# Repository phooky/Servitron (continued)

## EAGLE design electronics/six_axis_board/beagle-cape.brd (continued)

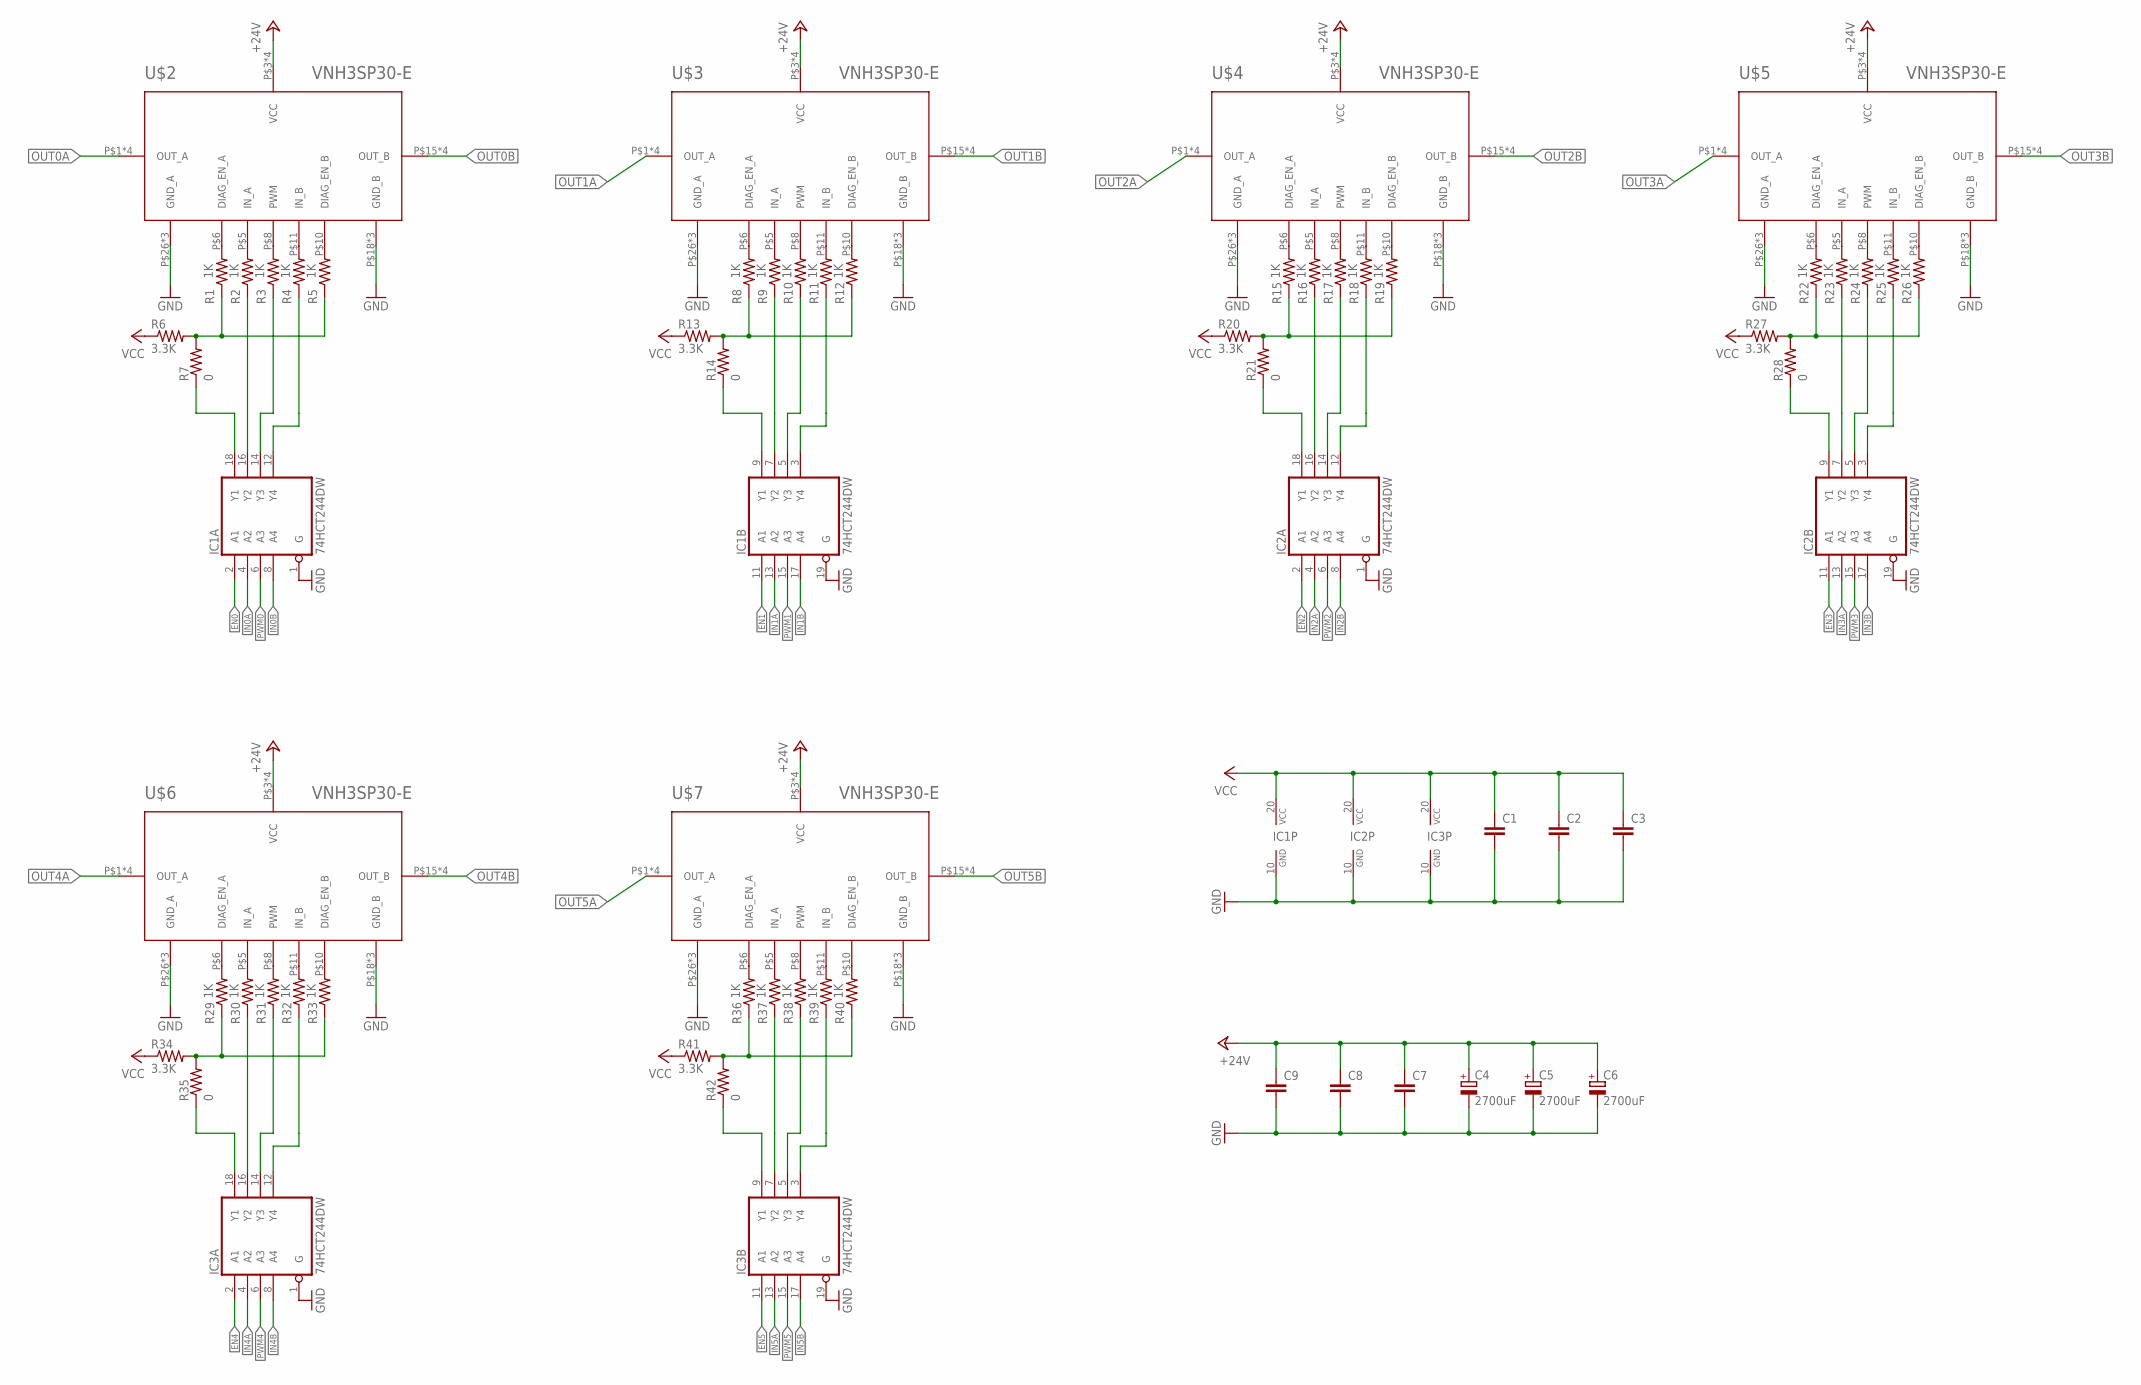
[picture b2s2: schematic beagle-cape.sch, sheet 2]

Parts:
C1, C2, C3, C7, C8, C9: C-EUC1206; C1206
C4, C5, C6: 2700uF; E5-13
IC1, IC2, IC3: 74HCT244DW; SO20W
R1, R2, R3, R4, R5, R8, R9, R10, R11, R12, R15, R16, R17, R18, R19, R22, R23, R24, R25, R26, R29, R30, R31, R32, R33, R36, R37, R38, R39, R40: 1K; R1206
R6, R13, R20, R27, R34, R41: 3.3K; R1206
R7, R14, R21, R28, R35, R42: 0; R1206
U$2, U$3, U$4, U$5, U$6, U$7: VNH3SP30-E; MULTIPOWER-SO-30

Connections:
+24V: C4.+, C5.+, C6.+, C7.1, C8.1, C9.1, U$2.P$3 (VCC), U$2.P$13 (VCC), U$2.P$23 (VCC), U$2.T$3 (VCC), U$3.P$3 (VCC), U$3.P$13 (VCC), U$3.P$23 (VCC), U$3.T$3 (VCC), U$4.P$3 (VCC), U$4.P$13 (VCC), U$4.P$23 (VCC), U$4.T$3 (VCC), U$5.P$3 (VCC), U$5.P$13 (VCC), U$5.P$23 (VCC), U$5.T$3 (VCC), U$6.P$3 (VCC), U$6.P$13 (VCC), U$6.P$23 (VCC), U$6.T$3 (VCC), U$7.P$3 (VCC), U$7.P$13 (VCC), U$7.P$23 (VCC), U$7.T$3 (VCC); also elsewhere on the board
EN0: IC1.2 (A1); also elsewhere on the board
EN1: IC1.11 (A1); also elsewhere on the board
EN2: IC2.2 (A1); also elsewhere on the board
EN3: IC2.11 (A1); also elsewhere on the board
EN4: IC3.2 (A1); also elsewhere on the board
EN5: IC3.11 (A1); also elsewhere on the board
GND: C1.2, C2.2, C3.2, C4.-, C5.-, C6.-, C7.2, C8.2, C9.2, IC1.1 (G), IC1.10 (GND), IC1.19 (G), IC2.1 (G), IC2.10 (GND), IC2.19 (G), IC3.1 (G), IC3.10 (GND), IC3.19 (G), U$2.P$18 (GND_B), U$2.P$19 (GND_B), U$2.P$20 (GND_B), U$2.P$26 (GND_A), U$2.P$27 (GND_A), U$2.P$28 (GND_A), U$3.P$18 (GND_B), U$3.P$19 (GND_B), U$3.P$20 (GND_B), U$3.P$26 (GND_A), U$3.P$27 (GND_A), U$3.P$28 (GND_A), U$4.P$18 (GND_B), U$4.P$19 (GND_B), U$4.P$20 (GND_B), U$4.P$26 (GND_A), U$4.P$27 (GND_A), U$4.P$28 (GND_A), U$5.P$18 (GND_B), U$5.P$19 (GND_B), U$5.P$20 (GND_B), U$5.P$26 (GND_A), U$5.P$27 (GND_A), U$5.P$28 (GND_A), U$6.P$18 (GND_B), U$6.P$19 (GND_B), U$6.P$20 (GND_B), U$6.P$26 (GND_A), U$6.P$27 (GND_A), U$6.P$28 (GND_A), U$7.P$18 (GND_B), U$7.P$19 (GND_B), U$7.P$20 (GND_B), U$7.P$26 (GND_A), U$7.P$27 (GND_A), U$7.P$28 (GND_A); also elsewhere on the board
IN0A: IC1.4 (A2); also elsewhere on the board
IN0B: IC1.8 (A4); also elsewhere on the board
IN1A: IC1.13 (A2); also elsewhere on the board
IN1B: IC1.17 (A4); also elsewhere on the board
IN2A: IC2.4 (A2); also elsewhere on the board
IN2B: IC2.8 (A4); also elsewhere on the board
IN3A: IC2.13 (A2); also elsewhere on the board
IN3B: IC2.17 (A4); also elsewhere on the board
IN4A: IC3.4 (A2); also elsewhere on the board
IN4B: IC3.8 (A4); also elsewhere on the board
IN5A: IC3.13 (A2); also elsewhere on the board
IN5B: IC3.17 (A4); also elsewhere on the board
unnamed: R1.2, U$2.P$6 (DIAG_EN_A)
unnamed: R1.1, R5.1, R6.2, R7.2
unnamed: IC1.18 (Y1), R7.1
unnamed: IC1.16 (Y2), R2.1
unnamed: IC1.14 (Y3), R3.1
unnamed: IC1.12 (Y4), R4.1
unnamed: R2.2, U$2.P$5 (IN_A)
unnamed: R3.2, U$2.P$8 (PWM)
unnamed: R4.2, U$2.P$11 (IN_B)
unnamed: R5.2, U$2.P$10 (DIAG_EN_B)
unnamed: R8.2, U$3.P$6 (DIAG_EN_A)
unnamed: R8.1, R12.1, R13.2, R14.2
unnamed: IC1.9 (Y1), R14.1
unnamed: IC1.7 (Y2), R9.1
unnamed: IC1.5 (Y3), R10.1
unnamed: IC1.3 (Y4), R11.1
unnamed: R39.2, U$7.P$11 (IN_B)
unnamed: R38.2, U$7.P$8 (PWM)
unnamed: R37.2, U$7.P$5 (IN_A)
unnamed: R40.2, U$7.P$10 (DIAG_EN_B)
unnamed: R15.2, U$4.P$6 (DIAG_EN_A)
unnamed: R15.1, R19.1, R20.2, R21.2
unnamed: IC2.18 (Y1), R21.1
unnamed: IC2.16 (Y2), R16.1
unnamed: IC2.14 (Y3), R17.1
unnamed: IC2.12 (Y4), R18.1
unnamed: R12.2, U$3.P$10 (DIAG_EN_B)
unnamed: R11.2, U$3.P$11 (IN_B)
unnamed: R16.2, U$4.P$5 (IN_A)
unnamed: R17.2, U$4.P$8 (PWM)
unnamed: R18.2, U$4.P$11 (IN_B)
unnamed: R19.2, U$4.P$10 (DIAG_EN_B)
unnamed: R22.2, U$5.P$6 (DIAG_EN_A)
unnamed: R22.1, R26.1, R27.2, R28.2
unnamed: IC2.9 (Y1), R28.1
unnamed: IC2.7 (Y2), R23.1
unnamed: IC2.5 (Y3), R24.1
unnamed: IC2.3 (Y4), R25.1
unnamed: R10.2, U$3.P$8 (PWM)
unnamed: R9.2, U$3.P$5 (IN_A)
unnamed: R29.2, U$6.P$6 (DIAG_EN_A)
unnamed: R29.1, R33.1, R34.2, R35.2
unnamed: IC3.18 (Y1), R35.1
unnamed: IC3.16 (Y2), R30.1
unnamed: IC3.14 (Y3), R31.1
unnamed: IC3.12 (Y4), R32.1
unnamed: R26.2, U$5.P$10 (DIAG_EN_B)
unnamed: R25.2, U$5.P$11 (IN_B)
unnamed: R30.2, U$6.P$5 (IN_A)
unnamed: R31.2, U$6.P$8 (PWM)
unnamed: R32.2, U$6.P$11 (IN_B)
unnamed: R33.2, U$6.P$10 (DIAG_EN_B)
unnamed: R36.2, U$7.P$6 (DIAG_EN_A)
unnamed: R36.1, R40.1, R41.2, R42.2
unnamed: IC3.9 (Y1), R42.1
unnamed: IC3.7 (Y2), R37.1
unnamed: IC3.5 (Y3), R38.1
unnamed: IC3.3 (Y4), R39.1
unnamed: R24.2, U$5.P$8 (PWM)
unnamed: R23.2, U$5.P$5 (IN_A)
OUT0A: U$2.P$1 (OUT_A), U$2.P$25 (OUT_A), U$2.P$30 (OUT_A), U$2.T$1 (OUT_A); also elsewhere on the board
OUT0B: U$2.P$15 (OUT_B), U$2.P$16 (OUT_B), U$2.P$21 (OUT_B), U$2.T$2 (OUT_B); also elsewhere on the board
OUT1A: U$3.P$1 (OUT_A), U$3.P$25 (OUT_A), U$3.P$30 (OUT_A), U$3.T$1 (OUT_A); also elsewhere on the board
OUT1B: U$3.P$15 (OUT_B), U$3.P$16 (OUT_B), U$3.P$21 (OUT_B), U$3.T$2 (OUT_B); also elsewhere on the board
OUT2A: U$4.P$1 (OUT_A), U$4.P$25 (OUT_A), U$4.P$30 (OUT_A), U$4.T$1 (OUT_A); also elsewhere on the board
OUT2B: U$4.P$15 (OUT_B), U$4.P$16 (OUT_B), U$4.P$21 (OUT_B), U$4.T$2 (OUT_B); also elsewhere on the board
OUT3A: U$5.P$1 (OUT_A), U$5.P$25 (OUT_A), U$5.P$30 (OUT_A), U$5.T$1 (OUT_A); also elsewhere on the board
OUT3B: U$5.P$15 (OUT_B), U$5.P$16 (OUT_B), U$5.P$21 (OUT_B), U$5.T$2 (OUT_B); also elsewhere on the board
OUT4A: U$6.P$1 (OUT_A), U$6.P$25 (OUT_A), U$6.P$30 (OUT_A), U$6.T$1 (OUT_A); also elsewhere on the board
OUT4B: U$6.P$15 (OUT_B), U$6.P$16 (OUT_B), U$6.P$21 (OUT_B), U$6.T$2 (OUT_B); also elsewhere on the board
OUT5A: U$7.P$1 (OUT_A), U$7.P$25 (OUT_A), U$7.P$30 (OUT_A), U$7.T$1 (OUT_A); also elsewhere on the board
OUT5B: U$7.P$15 (OUT_B), U$7.P$16 (OUT_B), U$7.P$21 (OUT_B), U$7.T$2 (OUT_B); also elsewhere on the board
PWM0: IC1.6 (A3); also elsewhere on the board
PWM1: IC1.15 (A3); also elsewhere on the board
PWM2: IC2.6 (A3); also elsewhere on the board
PWM3: IC2.15 (A3); also elsewhere on the board
PWM4: IC3.6 (A3); also elsewhere on the board
PWM5: IC3.15 (A3); also elsewhere on the board
VCC: C1.1, C2.1, C3.1, IC1.20 (VCC), IC2.20 (VCC), IC3.20 (VCC), R6.1, R13.1, R20.1, R27.1, R34.1, R41.1; also elsewhere on the board

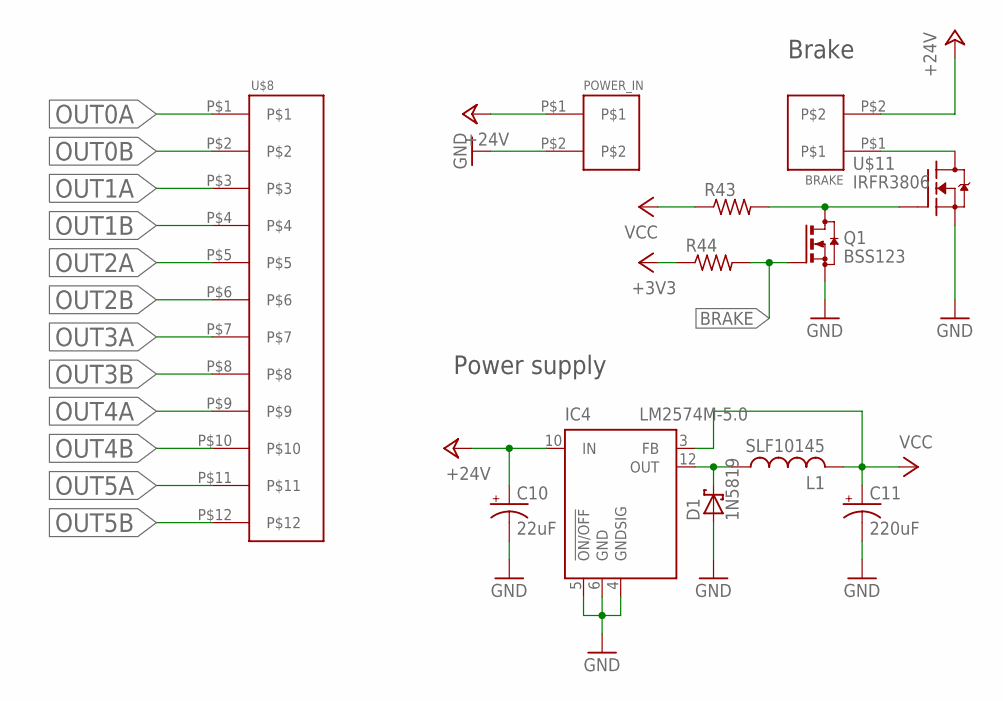
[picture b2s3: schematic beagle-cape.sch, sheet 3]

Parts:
BRAKE: PINHEAD-5MM-1X2; 5MM-HEADER-2
C10: 22uF; SANYO-OSCON_SMD_E7
C11: 220uF; SANYO-OSCON_SMD_F8
D1: 1N5819; SOD-123
IC4: LM2574M-5.0; SO14W
L1: SLF10145; SMD10145
POWER_IN: PINHEAD-5MM-1X2; 5MM-HEADER-2
Q1: BSS123; SOT23
R43, R44: R-US_R1206; R1206
U$8: PINHEAD-0.2IN-1X12; 0.2IN-TERMINAL-BLOCK-12
U$11: IRFR3806; TO252

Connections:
+3V3: R44.1; also elsewhere on the board
+24V: BRAKE.P$2, C10.+, IC4.10 (IN), POWER_IN.P$1; also elsewhere on the board
BRAKE: Q1.1 (G), R44.2; also elsewhere on the board
GND: C10.-, C11.-, D1.A, IC4.4 (GNDSIG), IC4.5 (!ON/OFF), IC4.6 (GND), POWER_IN.P$2, Q1.2 (S), U$11.2 (S); also elsewhere on the board
unnamed: D1.C, IC4.12 (OUT), L1.P$1 (1)
unnamed: BRAKE.P$1, U$11.3 (D)
unnamed: Q1.3 (D), R43.2, U$11.1 (G)
OUT0A: U$8.P$1; also elsewhere on the board
OUT0B: U$8.P$2; also elsewhere on the board
OUT1A: U$8.P$3; also elsewhere on the board
OUT1B: U$8.P$4; also elsewhere on the board
OUT2A: U$8.P$5; also elsewhere on the board
OUT2B: U$8.P$6; also elsewhere on the board
OUT3A: U$8.P$7; also elsewhere on the board
OUT3B: U$8.P$8; also elsewhere on the board
OUT4A: U$8.P$9; also elsewhere on the board
OUT4B: U$8.P$10; also elsewhere on the board
OUT5A: U$8.P$11; also elsewhere on the board
OUT5B: U$8.P$12; also elsewhere on the board
VCC: C11.+, IC4.3 (FB), L1.P$2 (2), R43.1; also elsewhere on the board

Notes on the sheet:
Power supply
Brake

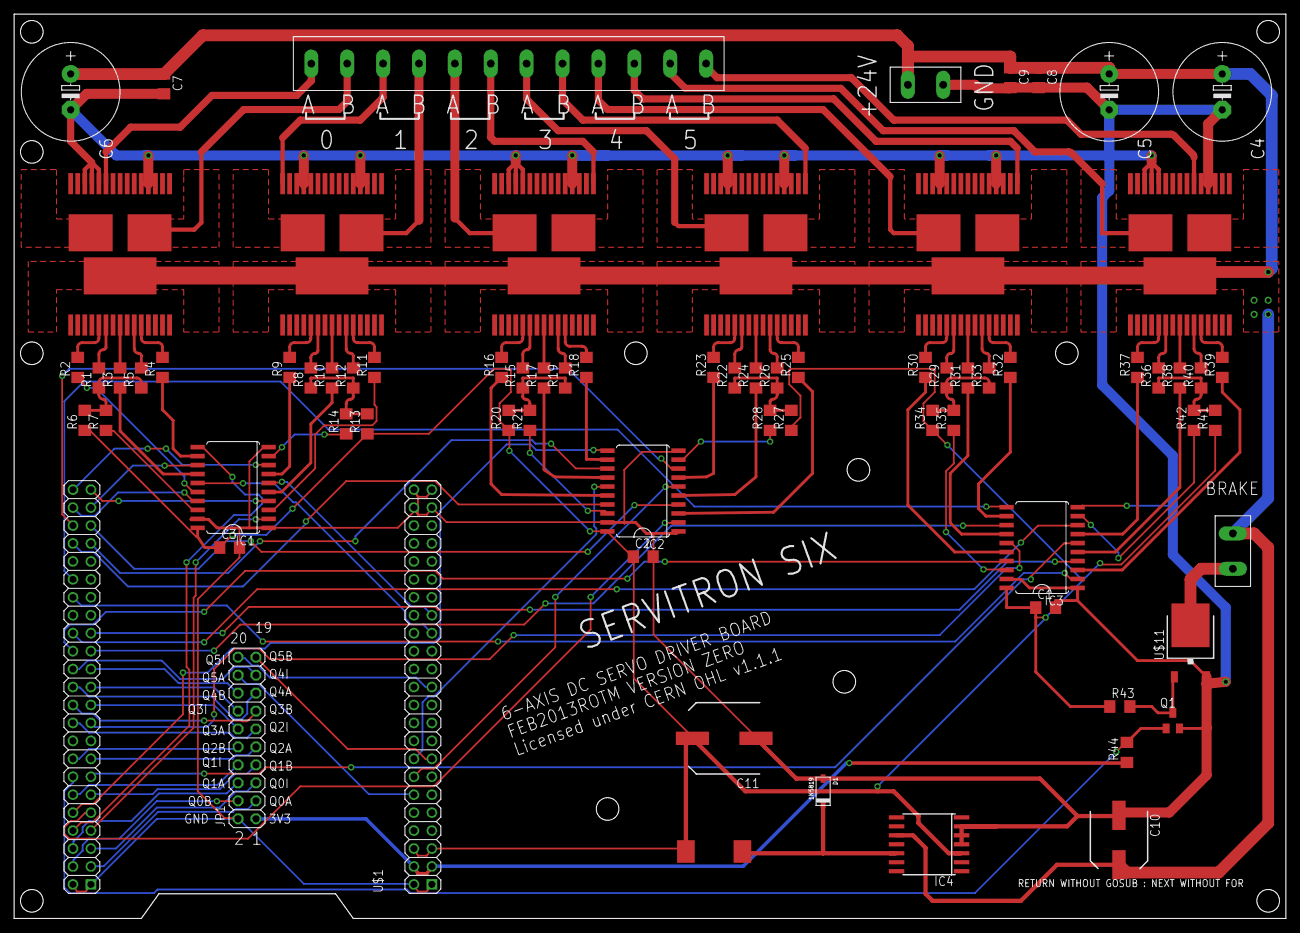
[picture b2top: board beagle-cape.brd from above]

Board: 2 copper layers, 180.0 x 128.0 mm, 74 parts (0 on the bottom side), 122 nets.

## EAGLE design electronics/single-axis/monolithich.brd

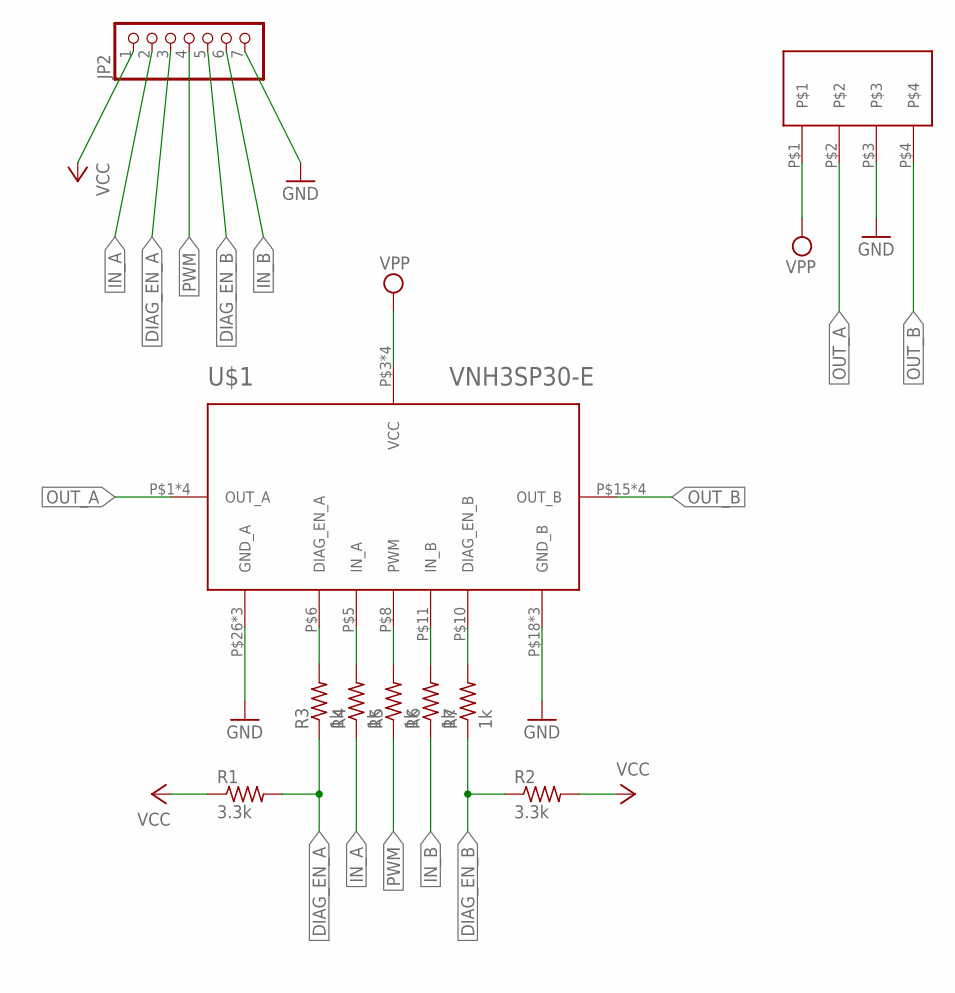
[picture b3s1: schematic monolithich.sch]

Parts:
JP2: PINHD-1X7; 1X07
R1, R2: 3.3k; R1206
R3, R4, R5, R6, R7: 1k; R1206
U$1: VNH3SP30-E; MULTIPOWER-SO-30
U$2: PINHEAD-5MM-1X4; 5MM-HEADER-4

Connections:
DIAG_EN_A: JP2.3, R1.2, R3.1
DIAG_EN_B: JP2.5, R2.1, R7.1
GND: JP2.7, U$1.P$18 (GND_B), U$1.P$19 (GND_B), U$1.P$20 (GND_B), U$1.P$26 (GND_A), U$1.P$27 (GND_A), U$1.P$28 (GND_A), U$2.P$3
IN_A: JP2.2, R4.1
IN_B: JP2.6, R6.1
unnamed: R3.2, U$1.P$6 (DIAG_EN_A)
unnamed: R4.2, U$1.P$5 (IN_A)
unnamed: R5.2, U$1.P$8 (PWM)
unnamed: R6.2, U$1.P$11 (IN_B)
unnamed: R7.2, U$1.P$10 (DIAG_EN_B)
OUT_A: U$1.P$1 (OUT_A), U$1.P$25 (OUT_A), U$1.P$30 (OUT_A), U$1.T$1 (OUT_A), U$2.P$2
OUT_B: U$1.P$15 (OUT_B), U$1.P$16 (OUT_B), U$1.P$21 (OUT_B), U$1.T$2 (OUT_B), U$2.P$4
PWM: JP2.4, R5.1
VCC: JP2.1, R1.1, R2.2
VPP: U$1.P$3 (VCC), U$1.P$13 (VCC), U$1.P$23 (VCC), U$1.T$3 (VCC), U$2.P$1

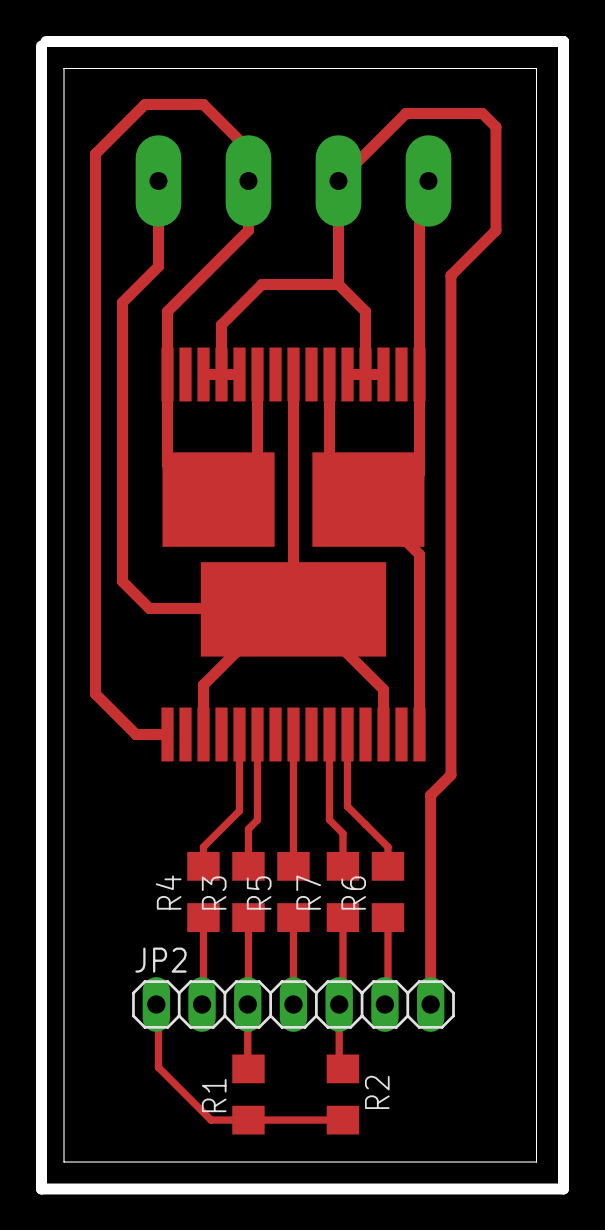
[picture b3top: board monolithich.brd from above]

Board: 2 copper layers, 26.2 x 60.8 mm, 10 parts (0 on the bottom side), 15 nets.

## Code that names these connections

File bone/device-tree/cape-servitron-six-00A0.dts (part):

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            brake_pins: pinmux_brake_pins{
                pinctrl-single,pins = <
                    // Mode is 0x0f: input off, pullup off
                    0x0d4 0xf // P8.33 - BRAKE - lcd_data13     GPIO0_9
                >;
            };
            motor_pins: pinmux_motor_pins{
                pinctrl-single,pins = <
                    // Mode is 0x0f: input off, pullup off
                    0x0d0 0xf // P8.35 - M_EN - lcd_data12      GPIO0_8
                    // M0
                    0x15c 0xf // P9.17 - M0_A  - spi0_cs0       GPIO0_5
                    0x040 0xf // P9.15 - M0_B  - gpmc_a0        GPIO1_16
                    0x158 0xf // P9.18 - M0_EN - spi0_d1        GPIO0_4
                    // M1
                    0x074 0xf // P9.13 - M1_A  - gpmc_wpn       GPIO0_31
                    0x070 0xf // P9.11 - M1_B  - gpmc_wait0     GPIO0_30
                    0x078 0xf // P9.12 - M1_EN - gpmc_ben1      GPIO1_28
                    // M2
                    0x180 0xf // P9.26 - M2_A  - uart1_rxd      GPIO0_14
                    0x184 0xf // P9.24 - M2_B  - uart1_txd      GPIO0_15
                    0x198 0xf // P9.30 - M2_EN - mcasp0_axr0    GPIO3_16
                    // M3
                    0x1a4 0xf // P9.27 - M3_A  - mcasp0_fsr     GPIO3_19
                    0x044 0xf // P9.23 - M3_B  - gpmc_a1        GPIO1_17
                    0x194 0xf // P9.29 - M3_EN - mcasp0_fsx     GPIO3_15
                    // M4
                    0x038 0xf // P8.16 - M4_A  - gpmc_ad14      GPIO1_14
                    0x028 0xf // P8.14 - M4_B  - gpmc_ad10      GPIO0_26
                    0x030 0xf // P8.12 - M4_EN - gpmc_ad12      GPIO1_12
                    // M5
                    0x034 0xf // P8.11 - M5_A  - gpmc_ad13      GPIO1_13
                    0x03c 0xf // P8.15 - M5_B  - gpmc_ad15      GPIO1_15
                    0x02c 0xf // P8.17 - M5_EN - gpmc_ad11      GPIO0_27
                >;
            };
            pruicss_quad_pins: pinmux_pruicss_quad_pins{
                pinctrl-single,pins = <
                    // Mode is 0x3f: input turned on, pullup off
                    0x090 0x3f // P8.7  - Q0A - gpmc_advn_ale   GPIO2_2
                    0x094 0x3f // P8.8  - Q0B - gpmc_oen_ren    GPIO2_3
                    0x09c 0x3f // P8.9  - Q0I - gpmc_ben0_cle   GPIO2_5

                    0x098 0x3f // P8.10 - Q1A - gpmc_wen        GPIO2_4
                    0x08c 0x3f // P8.18 - Q1B - gpmc_clk        GPIO2_1
                    0x0ec 0x3f // P8.30 - Q1I - lcd_ac_bias_en  GPIO2_25

                    0x0cc 0x3f // P8.34 - Q2A - lcd_data_11     GPIO2_17
                    0x0c8 0x3f // P8.36 - Q2B - lcd_data_10     GPIO2_16
                    0x0c0 0x3f // P8.37 - Q2I - lcd_data_8      GPIO2_14

                    0x0c4 0x3f // P8.38 - Q3A - lcd_data_9      GPIO2_15
                    0x0b8 0x3f // P8.39 - Q3B - lcd_data_6      GPIO2_12
                    0x0bc 0x3f // P8.40 - Q3I - lcd_data_7      GPIO2_13

                    0x0b0 0x3f // P8.41 - Q4A - lcd_data_4      GPIO2_10
                    0x0b4 0x3f // P8.42 - Q4B - lcd_data_5      GPIO2_11
                    0x0a8 0x3f // P8.43 - Q4I - lcd_data_2      GPIO2_8

                    0x0ac 0x3f // P8.44 - Q5A - lcd_data_3      GPIO2_9
                    0x0a0 0x3f // P8.45 - Q5B - lcd_data_0      GPIO2_6
                    0x0a4 0x3f // P8.46 - Q5I - lcd_data_1      GPIO2_7
                >;
            };

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        __overlay__ { status = "okay"; };
    };
    
    // Brake pin
    fragment@8 {
        target = <&ocp>;
        __overlay__ {
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                    gpios = <&gpio1 8 0>;
                    default-state = "on"; // active low
                };
                m0_a { label = "servitron:m0_a"; gpios = <&gpio1 5 0>; default-state = "off"; };
                m0_b { label = "servitron:m0_b"; gpios = <&gpio2 16 0>; default-state = "off"; };
                m0_en { label = "servitron:m0_en"; gpios = <&gpio1 4 0>; default-state = "off"; };

                m1_a { label = "servitron:m1_a"; gpios = <&gpio1 31 0>; default-state = "off"; };
                m1_b { label = "servitron:m1_b"; gpios = <&gpio1 30 0>; default-state = "off"; };
                m1_en { label = "servitron:m1_en"; gpios = <&gpio2 28 0>; default-state = "off"; };

                m2_a { label = "servitron:m2_a"; gpios = <&gpio1 14 0>; default-state = "off"; };
                m2_b { label = "servitron:m2_b"; gpios = <&gpio1 15 0>; default-state = "off"; };
                m2_en { label = "servitron:m2_en"; gpios = <&gpio4 16 0>; default-state = "off"; };

                m3_a { label = "servitron:m3_a"; gpios = <&gpio4 19 0>; default-state = "off"; };
                m3_b { label = "servitron:m3_b"; gpios = <&gpio2 17 0>; default-state = "off"; };
                m3_en { label = "servitron:m3_en"; gpios = <&gpio4 15 0>; default-state = "off"; };

                m4_a { label = "servitron:m4_a"; gpios = <&gpio2 14 0>; default-state = "off"; };
                m4_b { label = "servitron:m4_b"; gpios = <&gpio1 26 0>; default-state = "off"; };
                m4_en { label = "servitron:m4_en"; gpios = <&gpio2 12 0>; default-state = "off"; };

                m5_a { label = "servitron:m5_a"; gpios = <&gpio2 13 0>; default-state = "off"; };
                m5_b { label = "servitron:m5_b"; gpios = <&gpio2 15 0>; default-state = "off"; };
                m5_en { label = "servitron:m5_en"; gpios = <&gpio1 27 0>; default-state = "off"; };
            };

            motor_pwm0a {
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                pinctrl-names = "default";
                pinctrl-0 = <&brake_pins>;
                brake {
                    label = "servitron:brake";
                    gpios = <&gpio1 9 0>;
                    default-state = "on";
                };
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
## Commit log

2000-01-01 brake working.
2000-01-01 fix syntax issues
2000-01-01 getting motor tuned
2000-01-01 some sytax fixes to the device tree; appears to work
2000-01-01 fix: duplicate pinmux names
2000-01-01 inputs muxed. whew.
2000-01-01 increase power, motor enable
2000-01-01 adding waf script to build
2000-01-01 waf x perms
2000-01-01 basic motor enabled
2000-01-01 quadrature and reporting works
2012-11-22 It's "servItron", not "servotron".
2012-11-22 recovering from hosed repository (bad shutdown, yay)
2012-11-22 fix makefile; added retval in init
2013-01-21 Preparing repo
2013-02-16 package footprint gen script; library for various parts
2013-02-17 test board for vnh3sp30 driver
2013-02-18 pru test
2013-02-18 setting up test
2013-02-18 roughing out
2013-02-18 debugging.
2013-02-18 working demo, time to start in on real code
2013-02-19 framework for encoder
2013-02-19 reading io
2013-02-19 .bin is not a prereq of binary
2013-02-19 breaking out gpio defs and constructing header
2013-02-19 setting up quadrature
2013-02-19 limit runtime
2013-02-20 passing data; tracking bits
2013-02-20 counting works
2013-02-20 multichannel and some init, added errcount
2013-02-20 script for driving a vnh3sp30 off a teensy
2013-02-21 roughing out pwm stuff
2013-02-21 fixing up pwm rough
2013-02-21 starting in on proper servo system
2013-02-21 compiling; let's try it out
2013-02-25 tossing quadrature back in
2013-02-25 update to new include name
2013-02-25 whipping the PRU code back into shape
2013-02-25 close enough for quad test
2013-02-26 getting there but much muxing needs to be done
2013-02-26 Muxing. Fucking muxing.
2013-02-26 finally working quadrature on all six channels.
2013-02-26 cleanups, looking into event clearing
2013-02-26 fixed typo in quadrature.cc
2013-02-26 left out quad_test.cc
2013-02-26 adding rough motor stuff
2013-02-26 fix for typos
2013-02-27 motor test
2013-02-27 preparing motor test
2013-02-27 config motors
2013-02-28 refactor motor control
2013-02-28 refactor works.
2013-02-28 adding timer to quadrature loop
2013-03-02 adding trivial PID code
2013-03-02 an actual control loop. how quaint.
2013-03-02 testing on HW
2013-03-02 we have a basic control circuit running
2013-03-03 hexidecimal confusion!
2013-03-03 corrected pwm code for 1KHz
2013-03-03 adding json code changing some naming
2013-03-03 adding json configuration for pins
2013-03-03 json in progress; not too sure about this library...
2013-03-05 Revert "json in progress; not too sure about this library..."
    This reverts commit 4ccb8c7f9d803d58ed714bd0d1e0a7445f8ea2a7.
2013-03-05 Revert "adding json configuration for pins"
    This reverts commit 67b29facd51566a499498d9647407e0b9a27864d.
2013-03-05 json was a derail.
2013-03-05 starting in on actual code
2013-03-05 adding tests for PRU multiplication code
2013-03-05 16->32 bit multiply working, 32->64 bit has sign problems
2013-03-06 32->64 bit needs more testing but all seems welly
2013-03-06 sign marking variant
2013-03-06 moving tests out of root
2013-03-10 start on 32->32 multiply moved eagle library start work on complete six-axis servo board
2013-03-11 added 24V->5V converter, brake circuit
2013-03-12 schematic capture complete; board time
2013-03-14 initially laying out by hand
2013-03-14 more routing; auto the rest
2013-03-14 board layout is pretty much done and doc strings are in. prepping for production.
2013-03-14 putting under CERN OHL v1.1.1
2013-03-15 Added mounting holes Created board files for freedfm/4pcb (ac)
2013-04-01 old mission statement is old
2013-04-01 adding brake functionality
2013-04-01 brake working with actual board
2013-04-01 adding errata
2013-04-02 adding mounting for servitron six
2013-04-03 cleaning up tests
2013-04-23 moving brake test adding readme makefile updated to new pasm build
2013-04-23 point to right pasm for platform
2013-04-26 removing old PRU test
2013-04-26 removing old encoder test
2013-04-26 moving to top level (removing servo subdir)
2013-04-26 moving around source; trying waf
2013-04-27 moving test files
2013-04-27 adding c++ support
2013-04-27 basic waf script for brake test
2013-04-28 updating config (fix for 5/4 pwm switch)
2013-04-28 all axis working
2013-04-30 adding bone config script
2013-05-13 new readmy
2013-05-13 adding pru_sw as submodue building out new directories
2013-05-13 adding simple socket server
2013-05-13 added error checks on listen and accept
2013-05-13 moving in pin configuration and retooling basic server outline running
2013-05-13 trying to find pasm
2013-05-13 update submodule to reflect arm name change
2013-05-17 file structure for pinmuxing
2013-05-17 starting in on pinmuxing
2013-05-17 all pins muxed
2013-05-17 added missing motor muxes
2013-05-17 starting in on motor/pwm implementation
2013-05-18 beginning rough sketch of client
2013-05-18 checkpoint; most of the way to interoperating
2013-05-18 disappearing line restored
2013-05-18 fairly decent round trip
2013-05-20 adding getstatus stub
2013-05-20 tooing along with protocol
2013-05-21 starting in on multiplatform build
2013-05-21 working multiplatform build and stub implementation
2013-05-21 fixup server build; init motor and pinmux at startup
2013-05-22 open question
2013-05-23 keep screwing up the name
2013-05-23 rules for building pru asm
2013-07-12 adding beaglebone dts for reference
2013-07-12 adding more references
2013-07-17 adding initial start on devicetree file
2013-07-18 muxing and assignment for all quadrature encoder pins
2013-07-18 pinswaps
2013-07-19 bring gpio assignments up to date with muxing
2013-07-19 Upstream pasm changes
2013-07-19 rebuilding quad stuff
2013-07-19 bringing quad back up
2013-07-19 missing include for quad_shared
2013-07-19 remove unnecessary pin muxes (now done by device tree)
2013-07-19 -V2 for pasm
2013-07-19 workaround for 1-indexing in device tree
2013-07-20 moving pwm stuff in
2013-07-25 initial checkin of new cape
2013-07-26 added holes, layout mostly done
2013-07-27 added more heat sinking
2013-08-01 board sent out; cleaning up quadrature assembly
2013-08-01 finish cleanup/doc pass
2013-08-02 more doc, increment error count on state
2013-08-02 documenting plan for reporting
2013-08-02 adding report status and lock
2013-08-02 report build
2013-08-02 add report to c++ side
2013-08-10 report cycle usage
2013-08-10 renamed chips and output signals to match board placement and markings
2013-08-10 updated signals for current layout
2013-09-01 workaround for pasm comments
2013-09-01 add skip-report
2013-09-01 catch up on naming issue
2013-09-03 moving brake code around; adding brake to device tree as led
2013-09-03 adding motor muxing and pin selection
2013-09-09 enabling pwm_test
2013-09-09 set polarity to duty-high
2013-09-10 updating brake code
2013-09-10 adding motor control logic
2013-09-10 adding motor tests
2013-09-10 adding brake to motor test
2013-09-10 missing file
2013-09-10 removed obsolete pwm
2013-09-10 adding brake dep to motor test
2013-09-10 correct(?) pinouts
2013-09-11 setting frequency to 5KHz
2013-09-11 moving motors to float values
